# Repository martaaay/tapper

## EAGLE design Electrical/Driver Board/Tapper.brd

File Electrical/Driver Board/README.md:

Changes:
 - PCA9515B (i2c bus repeater) is currently SO-08 instead of TSSOP08
 - Need attachment lines for easy powering

Old Bugs:
The scheme of having one i2c line that goes to one motor driver and the 8-way i2c mux does not work because
the 8-way i2c mux exposes the i2c lines behind it to the master i2c line, which collides with the address of the one lone
motor sitting on the i2c line. In this scheme, to access a driver behind the mux, set EN for the I2C buffer to LOW and set the control
address on the MUX. To access the lone driver, set the control address on the MUX to 0 (no address exposed) and set EN on the I2C buffer to High.

Green LED info:
https://www.mouser.com/ProductDetail/638-192VGC

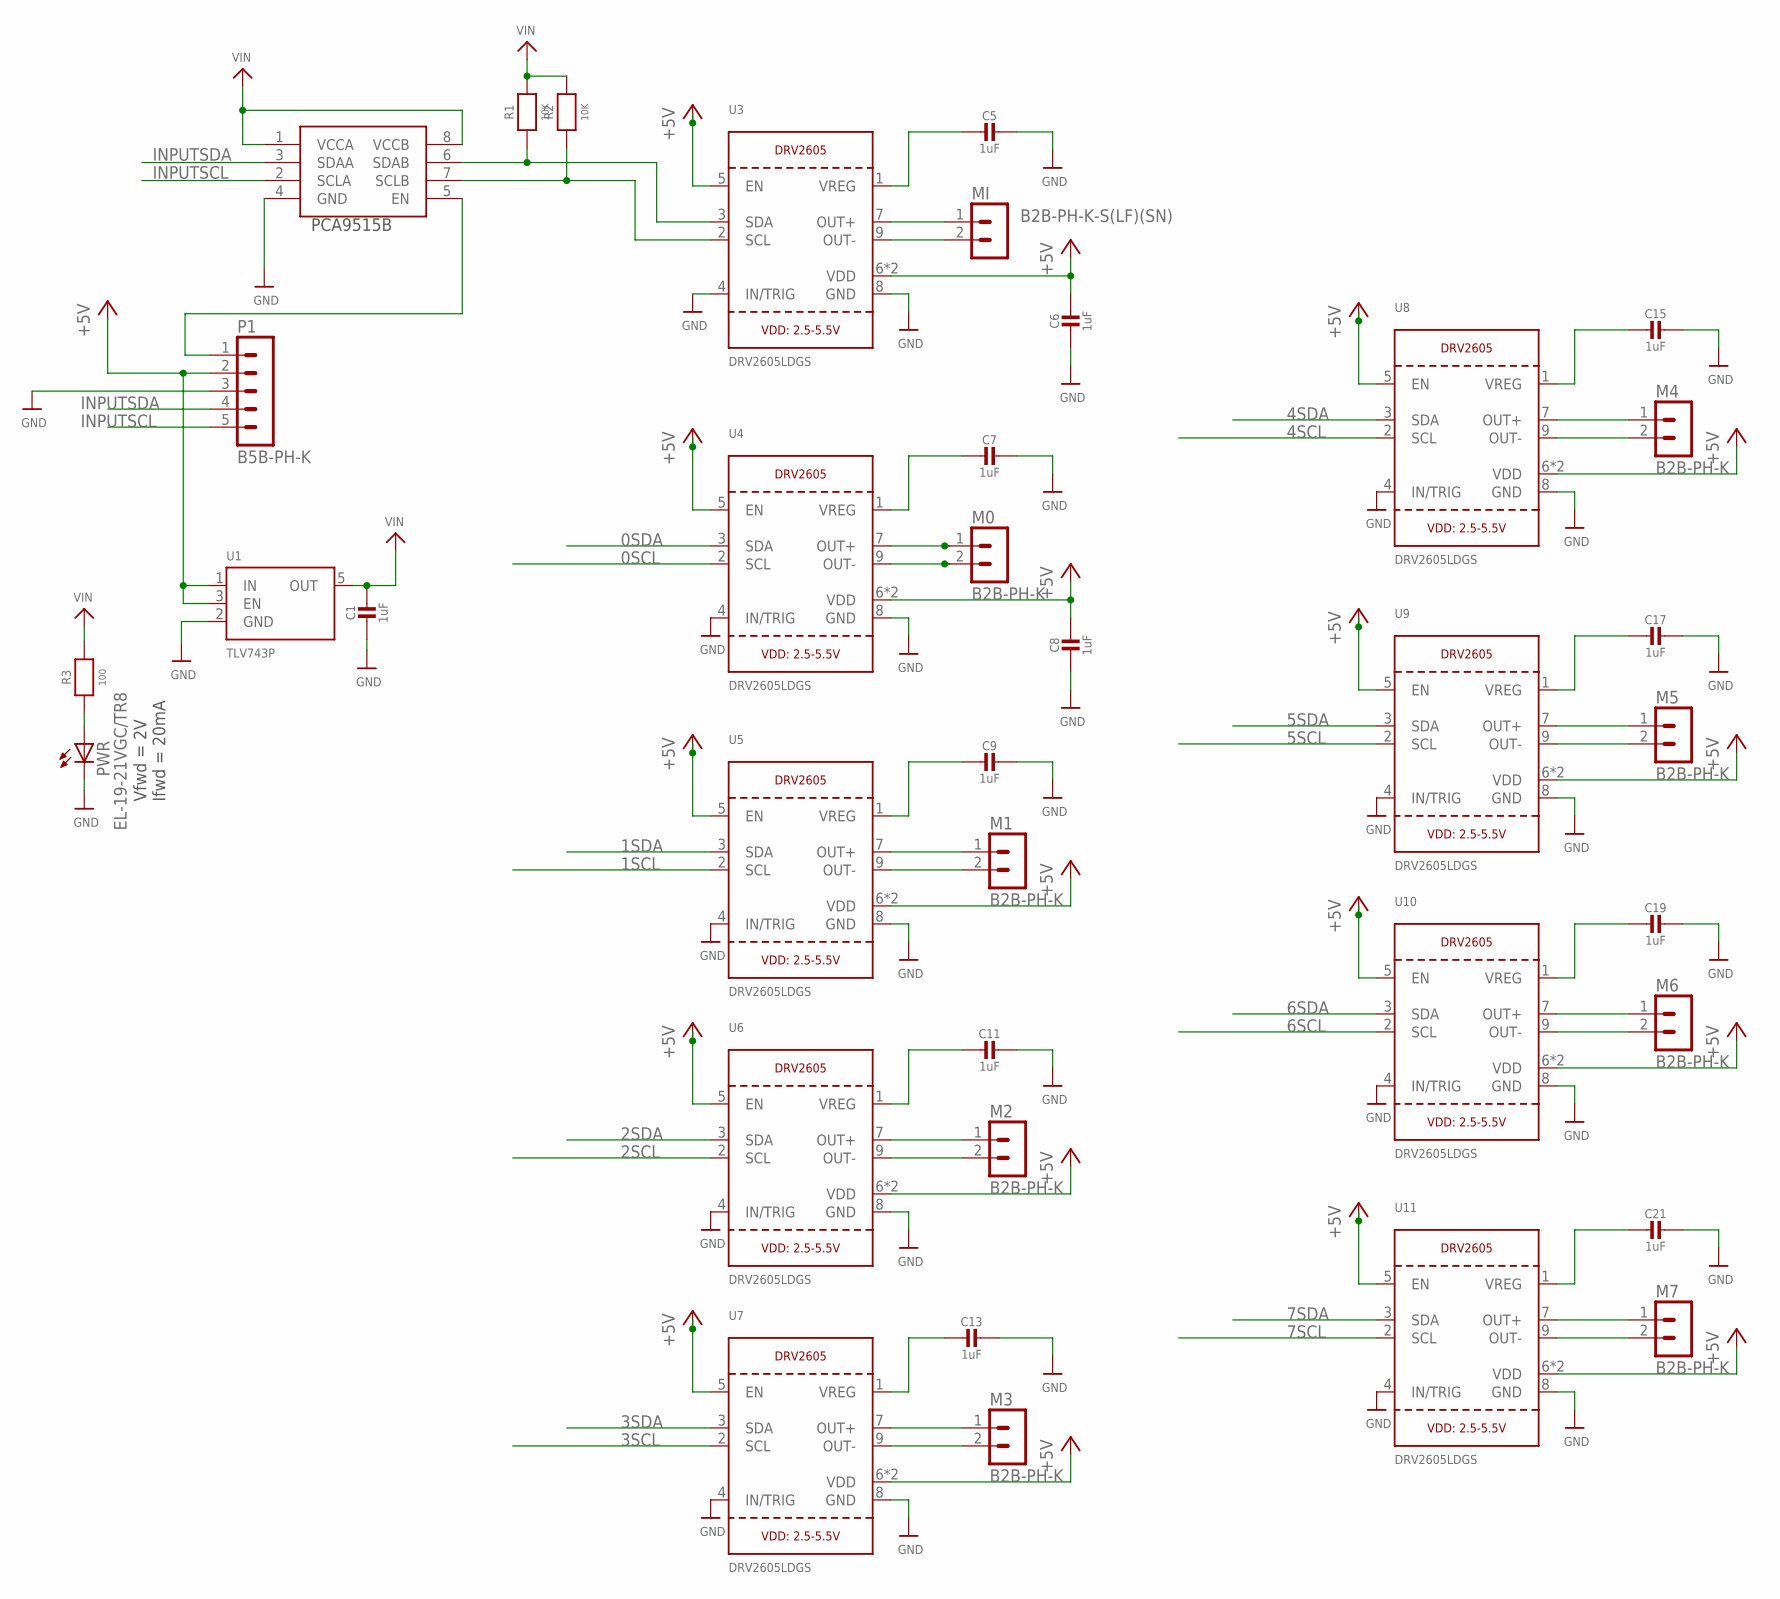
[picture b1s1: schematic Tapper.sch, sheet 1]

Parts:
C1, C5, C6, C7, C8, C9, C11, C13, C15, C17, C19, C21: 1uF; 0805-NO
M0, M1, M2, M3, M4, M5, M6, M7: B2B-PH-K
MI: B2B-PH-K-S(LF)(SN); B2B-PH-K
P1: B5B-PH-K
PWR: EL-19-21VGC/TR8; CHIP-LED0603
R1, R2: 10K; 0805-NO
R3: 100; 0805-NO
U1: TLV743P; SOT23-5
U3, U4, U5, U6, U7, U8, U9, U10, U11: DRV2605LDGS; PSOP10
U23: PCA9515B; SO-08

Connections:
0SCL: U4.2 (SCL); also elsewhere on the board
0SDA: U4.3 (SDA); also elsewhere on the board
1SCL: U5.2 (SCL); also elsewhere on the board
1SDA: U5.3 (SDA); also elsewhere on the board
2SCL: U6.2 (SCL); also elsewhere on the board
2SDA: U6.3 (SDA); also elsewhere on the board
3SCL: U7.2 (SCL); also elsewhere on the board
3SDA: U7.3 (SDA); also elsewhere on the board
4SCL: U8.2 (SCL); also elsewhere on the board
4SDA: U8.3 (SDA); also elsewhere on the board
5SCL: U9.2 (SCL); also elsewhere on the board
5SDA: U9.3 (SDA); also elsewhere on the board
6SCL: U10.2 (SCL); also elsewhere on the board
6SDA: U10.3 (SDA); also elsewhere on the board
7SCL: U11.2 (SCL); also elsewhere on the board
7SDA: U11.3 (SDA); also elsewhere on the board
+5V: C6.1, C8.1, P1.2, U1.1 (IN), U1.3 (EN), U3.5 (EN), U3.6 (VDD), U3.10 (VDD), U4.5 (EN), U4.6 (VDD), U4.10 (VDD), U5.5 (EN), U5.6 (VDD), U5.10 (VDD), U6.5 (EN), U6.6 (VDD), U6.10 (VDD), U7.5 (EN), U7.6 (VDD), U7.10 (VDD), U8.5 (EN), U8.6 (VDD), U8.10 (VDD), U9.5 (EN), U9.6 (VDD), U9.10 (VDD), U10.5 (EN), U10.6 (VDD), U10.10 (VDD), U11.5 (EN), U11.6 (VDD), U11.10 (VDD)
GND: C1.2, C5.1, C6.2, C7.1, C8.2, C9.1, C11.1, C13.1, C15.1, C17.1, C19.1, C21.1, P1.3, PWR.C, U1.2 (GND), U3.4 (IN/TRIG), U3.8 (GND), U4.4 (IN/TRIG), U4.8 (GND), U5.4 (IN/TRIG), U5.8 (GND), U6.4 (IN/TRIG), U6.8 (GND), U7.4 (IN/TRIG), U7.8 (GND), U8.4 (IN/TRIG), U8.8 (GND), U9.4 (IN/TRIG), U9.8 (GND), U10.4 (IN/TRIG), U10.8 (GND), U11.4 (IN/TRIG), U11.8 (GND), U23.4 (GND); also elsewhere on the board
INPUTSCL: P1.5, U23.2 (SCLA); also elsewhere on the board
INPUTSDA: P1.4, U23.3 (SDAA); also elsewhere on the board
unnamed: M0.2, U4.9 (OUT-)
unnamed: C5.2, U3.1 (VREG)
unnamed: C7.2, U4.1 (VREG)
unnamed: C9.2, U5.1 (VREG)
unnamed: P1.1, U23.5 (EN)
unnamed: C11.2, U6.1 (VREG)
unnamed: C13.2, U7.1 (VREG)
unnamed: C15.2, U8.1 (VREG)
unnamed: C17.2, U9.1 (VREG)
unnamed: C19.2, U10.1 (VREG)
unnamed: C21.2, U11.1 (VREG)
unnamed: R1.1, U3.3 (SDA), U23.6 (SDAB)
unnamed: R2.1, U3.2 (SCL), U23.7 (SCLB)
unnamed: PWR.A, R3.1
OUT+2: MI.1, U3.7 (OUT+)
OUT+3: M0.1, U4.7 (OUT+)
OUT+4: M1.1, U5.7 (OUT+)
OUT+5: M2.1, U6.7 (OUT+)
OUT+6: M3.1, U7.7 (OUT+)
OUT+7: M4.1, U8.7 (OUT+)
OUT+8: M5.1, U9.7 (OUT+)
OUT+9: M6.1, U10.7 (OUT+)
OUT+10: M7.1, U11.7 (OUT+)
OUT-2: MI.2, U3.9 (OUT-)
OUT-4: M1.2, U5.9 (OUT-)
OUT-5: M2.2, U6.9 (OUT-)
OUT-6: M3.2, U7.9 (OUT-)
OUT-7: M4.2, U8.9 (OUT-)
OUT-8: M5.2, U9.9 (OUT-)
OUT-9: M6.2, U10.9 (OUT-)
OUT-10: M7.2, U11.9 (OUT-)
VIN: C1.1, R1.2, R2.2, R3.2, U1.5 (OUT), U23.1 (VCCA), U23.8 (VCCB); also elsewhere on the board

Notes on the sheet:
PCA9515B
Vfwd = 2V Ifwd = 20mA

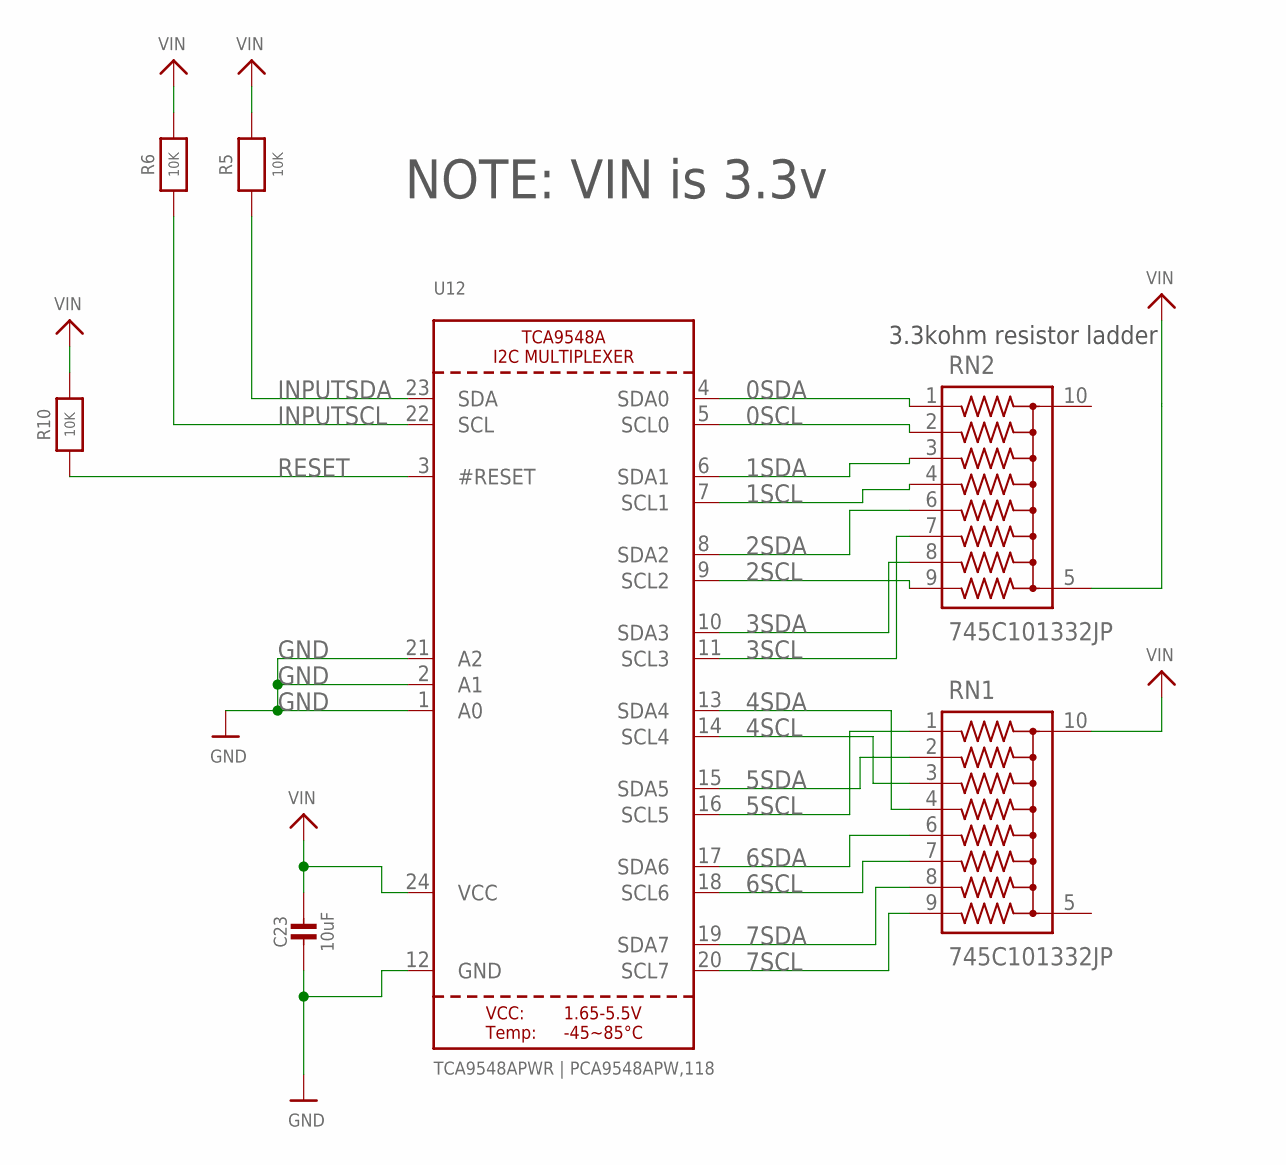
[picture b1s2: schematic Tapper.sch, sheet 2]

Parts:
C23: 10uF; 0805-NO
R5, R6: 10K; 0805-NO
R10: 10K; _0805MP
RN1, RN2: 745C101332JP; 745-10NS
U12: TCA9548APWR | PCA9548APW,118; TSSOP24

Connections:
0SCL: RN2.2, U12.5 (SCL0); also elsewhere on the board
0SDA: RN2.1, U12.4 (SDA0); also elsewhere on the board
1SCL: RN2.4, U12.7 (SCL1); also elsewhere on the board
1SDA: RN2.3, U12.6 (SDA1); also elsewhere on the board
2SCL: RN2.9, U12.9 (SCL2); also elsewhere on the board
2SDA: RN2.6, U12.8 (SDA2); also elsewhere on the board
3SCL: RN2.7, U12.11 (SCL3); also elsewhere on the board
3SDA: RN2.8, U12.10 (SDA3); also elsewhere on the board
4SCL: RN1.3, U12.14 (SCL4); also elsewhere on the board
4SDA: RN1.4, U12.13 (SDA4); also elsewhere on the board
5SCL: RN1.1, U12.16 (SCL5); also elsewhere on the board
5SDA: RN1.2, U12.15 (SDA5); also elsewhere on the board
6SCL: RN1.7, U12.18 (SCL6); also elsewhere on the board
6SDA: RN1.6, U12.17 (SDA6); also elsewhere on the board
7SCL: RN1.9, U12.20 (SCL7); also elsewhere on the board
7SDA: RN1.8, U12.19 (SDA7); also elsewhere on the board
GND: C23.2, U12.1 (A0), U12.2 (A1), U12.12 (GND), U12.21 (A2); also elsewhere on the board
INPUTSCL: R6.1, U12.22 (SCL); also elsewhere on the board
INPUTSDA: R5.1, U12.23 (SDA); also elsewhere on the board
RESET: R10.1, U12.3 (#RESET)
VIN: C23.1, R5.2, R6.2, R10.2, RN1.10, RN2.5, U12.24 (VCC); also elsewhere on the board

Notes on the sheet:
3.3kohm resistor ladder
NOTE: VIN is 3.3v

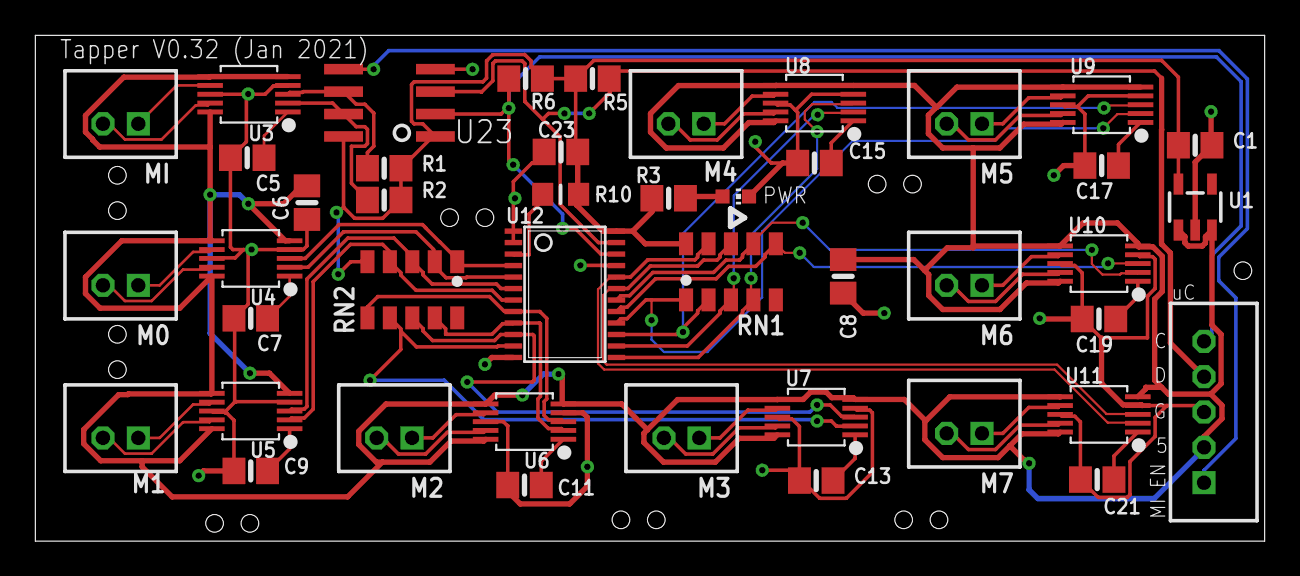
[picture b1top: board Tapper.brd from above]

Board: 2 copper layers, 69.6 x 28.6 mm, 44 parts (0 on the bottom side), 53 nets.

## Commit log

2017-06-06 Initial
2017-06-18 Add initial stuff
2017-06-18 Display and multi channel working
2017-07-10 Add standby to reduce heating
2021-09-01 Add requirements.txt
2021-09-01 Update for the current world
2021-12-17 Organize and add mechanical/electrical
2021-12-17 Cleanup
2021-12-17 Add Mechanical readme
2021-12-30 0.3v draft layout
2021-12-30 Board RC1
2021-12-30 Add .gitignore
2021-12-31 More improvements
2022-01-18 v0.31: Minor routing tweak
2022-01-19 i2c bus chip PI4MSD5V9547LEX is NOT the same as TCA9548APWR. It may be made to run similar, but, for instance, it has a different control register that doesnt allow for simultaneous writing to multip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
2022-01-20 BIG OOPS: Need 9 drivers, but mux only handles 8. The extra one was hung off the main i2c line with the mux assuming that the mux would be on 0x70 and the driver on 0x5a, but the mux exposes the driv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
2022-01-21 0.32: Add 3v3 reg, remove disp, add buffer for (hopefully) enabling the lone driver
2022-01-21 Add power led
2022-02-13 Working

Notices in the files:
parts and their libraries:
microbuilder: This work is placed in the public domain, and may be freely used for commercial and non-commercial work with the following conditions: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
resistor-array: Copyright (C) 2008, Bob Starr
con-jst-ph: Copyright (C) 2016, Bob Starr
